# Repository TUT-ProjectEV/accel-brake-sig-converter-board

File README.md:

# accel-brake-sig-converter-board

## Revision
- v1.0

## Overview
- This board converts the sensor output VOLTAGE signal into the CURRENT signal
    - 4~20mA

## Requirement
### Development
- Kicad 8.0
### Libraries
- ProjectEV-Kicad-Library
    - v8.0

## Usage
- J1, J2, J3: Connect to Controller or ADC and Power supply
    - Pin 1: +12V Input
    - Pin 2: GND
    - Pin 3: Current Signal Output
- J4, J5, J6: Connect to Sensor
    - Pin 1: +5V Output
    - Pin 2: GND
    - Pin 3: Voltage Signal Input

## Features
- Input Signal Voltage Range: +1~+5V
- Output Signal Current Range: 4~20mA
    - 250 Ohms termination: +1~+5V

## Reference
- ["Reference Site Name"]("Reference URL")

## Author
- [ST04-tkmr](https://github.com/ST04-tkmr)

## License
- Copyright (c) 2024 東京工科大学 ProjectEV

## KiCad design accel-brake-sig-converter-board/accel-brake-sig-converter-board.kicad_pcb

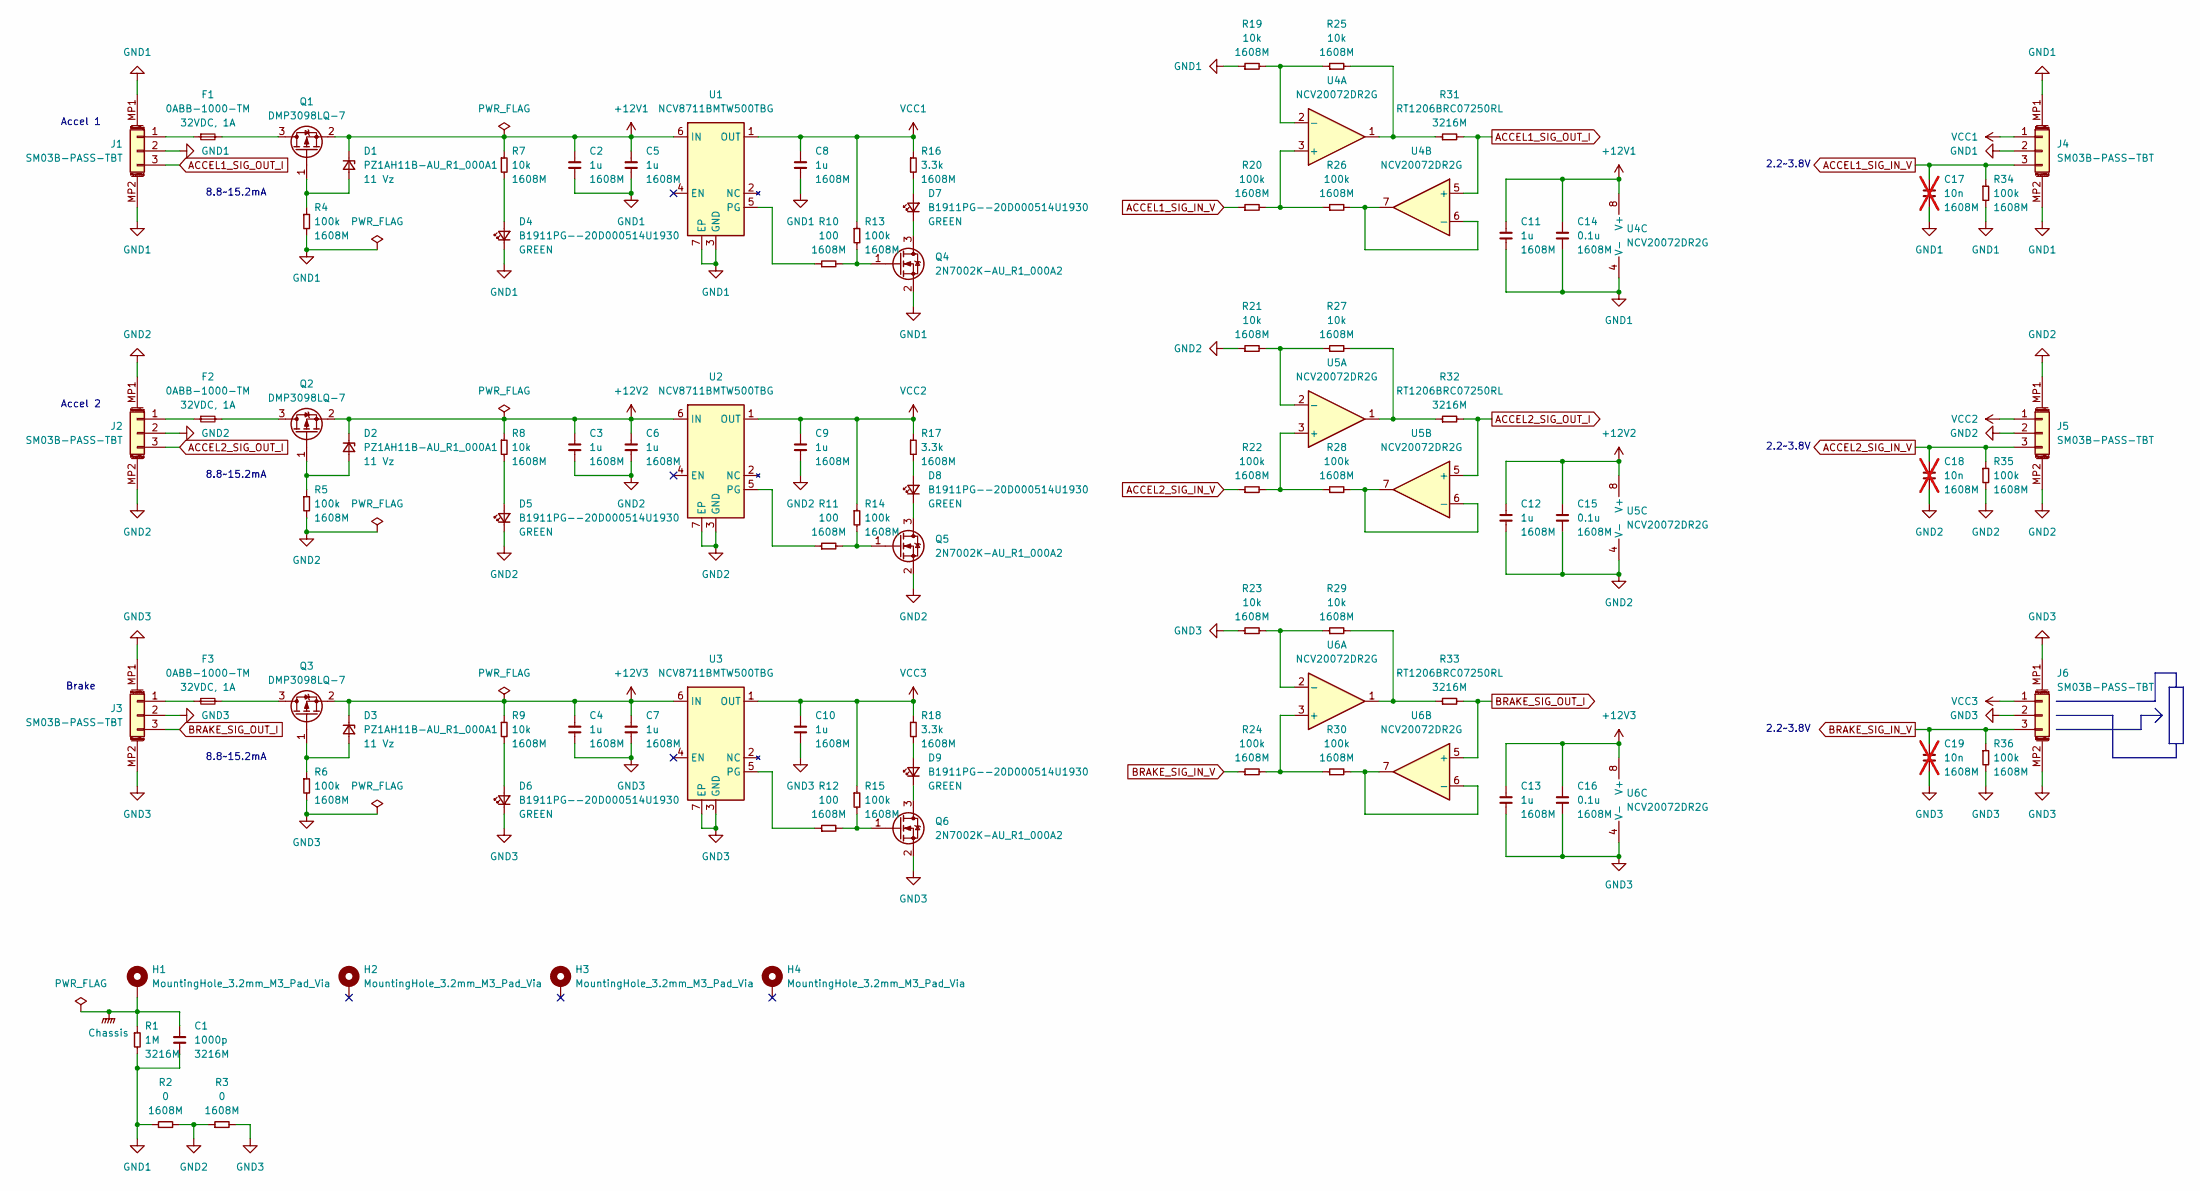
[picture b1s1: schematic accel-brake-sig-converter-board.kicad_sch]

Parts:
C1: 1000p; C_3216M
C2, C3, C4, C5, C6, C7, C8, C9, C10, C11, C12, C13: 1u; C_1608M
C14, C15, C16: 0.1u; C_1608M
C17, C18, C19: 10n; C_1608M; not fitted
D1, D2, D3: PZ1AH11B-AU_R1_000A1; Mouser番号 241-PZ1AH11BAUR1000A
D4, D5, D6, D7, D8, D9: B1911PG--20D000514U1930; digikey品番 3147-B1911PG--20D000514U1930CT-ND
F1, F2, F3: 0ABB-1000-TM; digikey品番 507-0ABB-5000-TMCT-ND
H1, H2, H3, H4: MountingHole_3.2mm_M3_Pad_Via
J1, J2, J3, J4, J5, J6: SM03B-PASS-TBT; digikey品番 455-SM03B-PASS-TBTCT-ND
Q1, Q2, Q3: DMP3098LQ-7; Mouser番号 621-DMP3098LQ-7
Q4, Q5, Q6: 2N7002K-AU_R1_000A2; digikey品番 3757-2N7002K-AU_R1_000A2CT-ND
R1: 1M; R_3216M
R2, R3: 0; R_1608M
R4, R5, R6, R13, R14, R15, R20, R22, R24, R26, R28, R30, R34, R35, R36: 100k; R_1608M
R7, R8, R9, R19, R21, R23, R25, R27, R29: 10k; R_1608M
R10, R11, R12: 100; R_1608M
R16, R17, R18: 3.3k; R_1608M
R31, R32, R33: RT1206BRC07250RL; Mouser番号 603-RT1206BRC07250RL
U1, U2, U3: NCV8711BMTW500TBG; Mouser番号 863-NCV8711BMTW500TB
U4, U5, U6: NCV20072DR2G; Mouser番号 863-NCV20072DR2G

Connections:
+12V1: C2.1, C5.1, C11.1, C14.1, D1.1 (K), Q1.2 (S), R7.1, U1.6 (IN), U4.8 (V+)
+12V2: C3.1, C6.1, C12.1, C15.1, D2.1 (K), Q2.2 (S), R8.1, U2.6 (IN), U5.8 (V+)
+12V3: C4.1, C7.1, C13.1, C16.1, D3.1 (K), Q3.2 (S), R9.1, U3.6 (IN), U6.8 (V+)
ACCEL1_SIG_IN_V: C17.1, J4.3, R20.1, R34.1
ACCEL1_SIG_OUT_I: J1.3, R31.2, U4.5 (+)
ACCEL2_SIG_IN_V: C18.1, J5.3, R22.1, R35.1
ACCEL2_SIG_OUT_I: J2.3, R32.2, U5.5 (+)
BRAKE_SIG_IN_V: C19.1, J6.3, R24.1, R36.1
BRAKE_SIG_OUT_I: J3.3, R33.2, U6.5 (+)
Chassis: C1.1, H1.MP, R1.1
GND1: C1.2, C2.2, C5.2, C8.2, C11.2, C14.2, C17.2, D4.1 (K), J1.2, J1.MP1 (MountPin), J1.MP2 (MountPin), J4.2, J4.MP1 (MountPin), J4.MP2 (MountPin), Q4.2 (S), R1.2, R2.1, R4.2, R19.1, R34.2, U1.3 (GND), U1.7 (EP), U4.4 (V-)
GND2: C3.2, C6.2, C9.2, C12.2, C15.2, C18.2, D5.1 (K), J2.2, J2.MP1 (MountPin), J2.MP2 (MountPin), J5.2, J5.MP1 (MountPin), J5.MP2 (MountPin), Q5.2 (S), R2.2, R3.1, R5.2, R21.1, R35.2, U2.3 (GND), U2.7 (EP), U5.4 (V-)
GND3: C4.2, C7.2, C10.2, C13.2, C16.2, C19.2, D6.1 (K), J3.2, J3.MP1 (MountPin), J3.MP2 (MountPin), J6.2, J6.MP1 (MountPin), J6.MP2 (MountPin), Q6.2 (S), R3.2, R6.2, R23.1, R36.2, U3.3 (GND), U3.7 (EP), U6.4 (V-)
unnamed: D1.2 (A), Q1.1 (G), R4.1
unnamed: D2.2 (A), Q2.1 (G), R5.1
unnamed: D3.2 (A), Q3.1 (G), R6.1
unnamed: D4.2 (A), R7.2
unnamed: D5.2 (A), R8.2
unnamed: D6.2 (A), R9.2
unnamed: D7.2 (A), R16.2
unnamed: D7.1 (K), Q4.3 (D)
unnamed: D8.2 (A), R17.2
unnamed: D8.1 (K), Q5.3 (D)
unnamed: D9.2 (A), R18.2
unnamed: D9.1 (K), Q6.3 (D)
unnamed: F1.1, J1.1
unnamed: F2.1, J2.1
unnamed: F3.1, J3.1
unnamed: F1.2, Q1.3 (D)
unnamed: F2.2, Q2.3 (D)
unnamed: F3.2, Q3.3 (D)
unnamed: Q4.1 (G), R10.2, R13.2
unnamed: Q5.1 (G), R11.2, R14.2
unnamed: Q6.1 (G), R12.2, R15.2
unnamed: R25.2, R31.1, U4.1
unnamed: R27.2, R32.1, U5.1
unnamed: R29.2, R33.1, U6.1
unnamed: R10.1, U1.5 (PG)
unnamed: R11.1, U2.5 (PG)
unnamed: R12.1, U3.5 (PG)
unnamed: R20.2, R26.1, U4.3 (+)
unnamed: R19.2, R25.1, U4.2 (-)
unnamed: R26.2, U4.6 (-), U4.7
unnamed: R22.2, R28.1, U5.3 (+)
unnamed: R21.2, R27.1, U5.2 (-)
unnamed: R28.2, U5.6 (-), U5.7
unnamed: R24.2, R30.1, U6.3 (+)
unnamed: R23.2, R29.1, U6.2 (-)
unnamed: R30.2, U6.6 (-), U6.7
VCC1: C8.1, J4.1, R13.1, R16.1, U1.1 (OUT)
VCC2: C9.1, J5.1, R14.1, R17.1, U2.1 (OUT)
VCC3: C10.1, J6.1, R15.1, R18.1, U3.1 (OUT)

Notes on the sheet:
Brake
8.8~15.2mA
2.2~3.8V
Accel 1
Accel 2

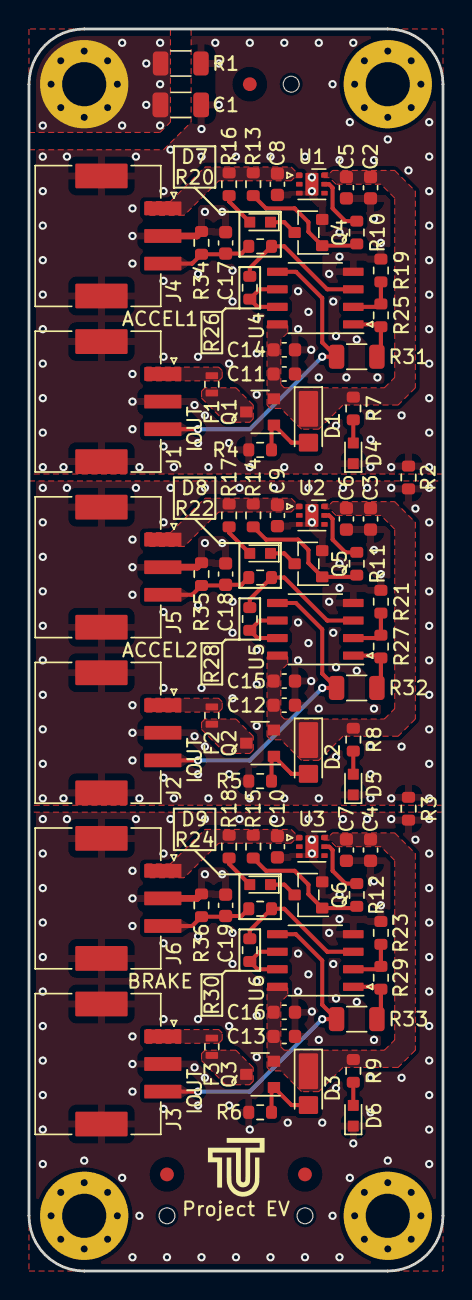
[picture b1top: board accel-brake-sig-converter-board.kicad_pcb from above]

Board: 2 copper layers, 30.0 x 90.0 mm, 89 parts (0 on the bottom side), 52 nets.

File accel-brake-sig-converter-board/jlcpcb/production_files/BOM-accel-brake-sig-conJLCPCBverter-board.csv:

Comment,Designator,Footprint,LCSC
0.1u,"C14,C15,C16",C_1608M,C14663
1u,"C10,C11,C12,C13,C2,C3,C4,C5,C6,C7,C8,C9",C_1608M,C15849
1M,R1,R_3216M,C17927
0,"R2,R3",R_1608M,C21189
100,"R10,R11,R12",R_1608M,C22775
3.3k,"R16,R17,R18",R_1608M,C22978
100k,"R13,R14,R15,R20,R22,R24,R26,R28,R30,R34,R35,R36,R4,R5,R6",R_1608M,C25803
10k,"R19,R21,R23,R25,R27,R29,R7,R8,R9",R_1608M,C25804
10n,"C17,C18,C19",C_1608M,C57112
1000p,C1,C_3216M,C9196

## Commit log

2024-07-28 Initialize main
2024-08-05 create project
2024-08-05 add title, date, revision
2024-08-05 add ignore folder
2024-08-08 create sch, add power circuit
2024-08-09 信号処理部追加
2024-08-10 ブレーキセンサ部以外完成
2024-08-12 回路図完成
2024-08-12 update symbol
2024-08-12 素子配置ACCEL1まで
2024-08-13 配置およそ完了
2024-08-13 配置完了
2024-08-14 accel1配線
2024-08-14 配線完了, DRC完了
2024-08-14 add fiducials, toolingholes
2024-08-16 JLCPCB素子選定
2024-08-16 generate production files by JLCPCB Tools
2024-08-16 generate pdf of sch, gerber
2024-08-16 rename
2024-08-16 generate 3dmodel
2024-08-18 add JLCPCB PCBA parts list
2024-08-20 add JLCPCB PCBA list
2024-08-20 generate BOM
2024-08-20 create BOM for Mouser
2024-09-04 README.md を更新
